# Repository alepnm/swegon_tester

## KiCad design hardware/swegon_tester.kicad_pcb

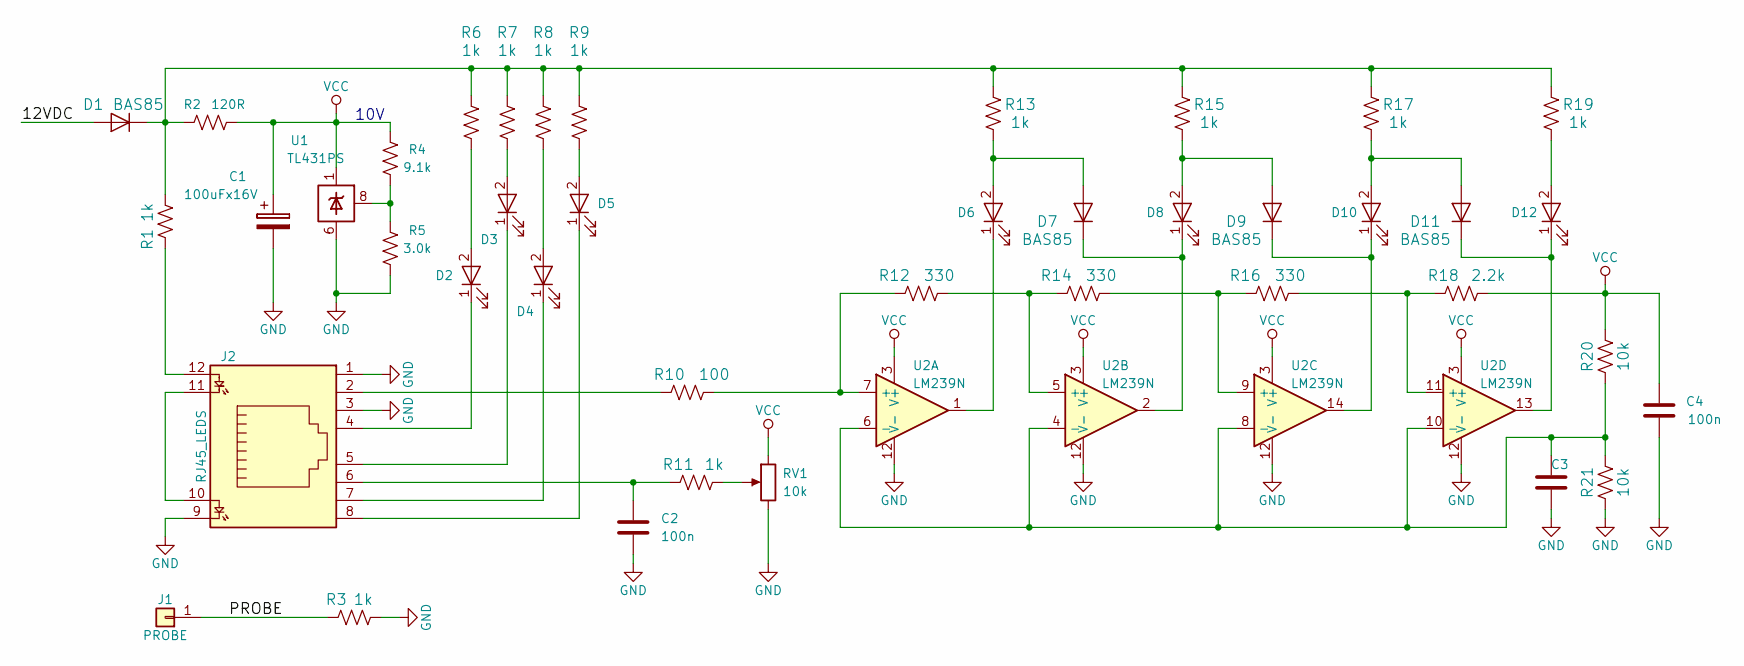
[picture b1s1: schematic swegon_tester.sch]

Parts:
C1: 100uFx16V; CP_Radial_D6.3mm_P2.50mm
C2, C3, C4: 100n; C_0805
D1, D7, D9, D11: BAS85; D_MiniMELF
D2: PIN4; LED_D3.0mm
D3: PIN5; LED_D3.0mm
D4: PIN7; LED_D3.0mm
D5: PIN8; LED_D3.0mm
D6: 2.6K; LED_D3.0mm
D8: 1.9K; LED_D3.0mm
D10: 1.2K; LED_D3.0mm
D12: 680R; LED_D3.0mm
J1: PROBE; SolderWirePad_2x_1mmDrill
J2: RJ45_LEDS; RJHSE538X
R1, R3, R6, R7, R8, R9, R11, R13, R15, R17, R19: 1k; R_0805
R2: 120R; R_1206
R4: 9.1k; R_0805
R5: 3.0k; R_0805
R10: 100; R_0805
R12, R14, R16: 330; R_0805
R18: 2.2k; R_0805
R20, R21: 10k; R_0805
RV1: 10k; Potentiometer_Trimmer_ACP_CA6v_Horizontal
U1: TL431PS; SOIC-8_3.9x4.9mm_Pitch1.27mm
U2: LM239N; DIP-14_W7.62mm

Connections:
/12VDC: D1.2 (A)
/PROBE: J1.1, R3.1
GND: C1.2, C2.2, C3.1, C4.1, J2.1, J2.3, J2.9, R3.2, R5.1, R21.1, RV1.3, U1.2, U1.3, U1.6 (A), U1.7, U2.12 (V-)
unnamed: C2.1, J2.6, R11.1
unnamed: C3.2, R20.1, R21.2, U2.4 (-), U2.6 (-), U2.8 (-), U2.10 (-)
unnamed: D1.1 (K), R1.2, R2.1, R6.2, R7.2, R8.2, R9.2, R13.2, R15.2, R17.2, R19.2
unnamed: D2.1 (K), J2.4
unnamed: D2.2 (A), R6.1
unnamed: D3.1 (K), J2.5
unnamed: D3.2 (A), R7.1
unnamed: D4.1 (K), J2.7
unnamed: D4.2 (A), R8.1
unnamed: D5.1 (K), J2.8
unnamed: D5.2 (A), R9.1
unnamed: D6.1 (K), U2.1
unnamed: D6.2 (A), D7.2 (A), R13.1
unnamed: D7.1 (K), D8.1 (K), U2.2
unnamed: D8.2 (A), D9.2 (A), R15.1
unnamed: D9.1 (K), D10.1 (K), U2.14
unnamed: D10.2 (A), D11.2 (A), R17.1
unnamed: D11.1 (K), D12.1 (K), U2.13
unnamed: D12.2 (A), R19.1
unnamed: J2.2, R10.1
unnamed: J2.10, J2.11
unnamed: J2.12, R1.1
unnamed: R4.1, R5.2, U1.8 (G)
unnamed: R10.2, R12.1, U2.7 (+)
unnamed: R11.2, RV1.2
unnamed: R12.2, R14.1, U2.5 (+)
unnamed: R14.2, R16.1, U2.9 (+)
unnamed: R16.2, R18.1, U2.11 (+)
VCC: C1.1, C4.2, R2.2, R4.2, R18.2, R20.2, RV1.1, U1.1 (C), U2.3 (V+)

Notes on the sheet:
10V

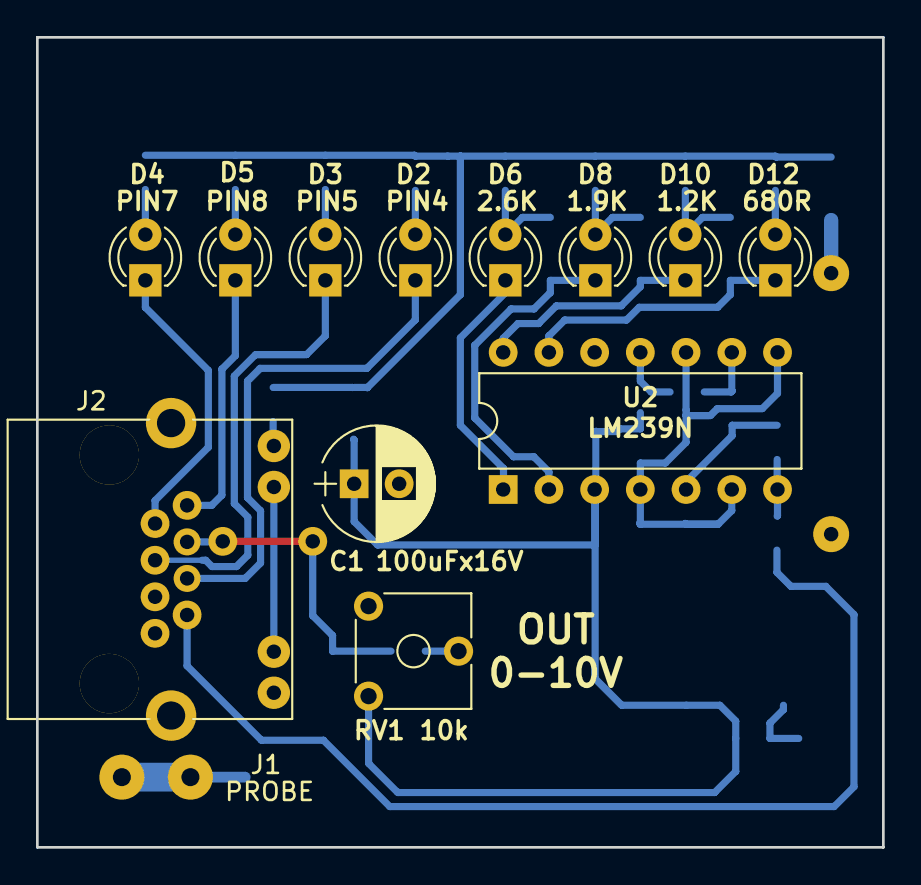
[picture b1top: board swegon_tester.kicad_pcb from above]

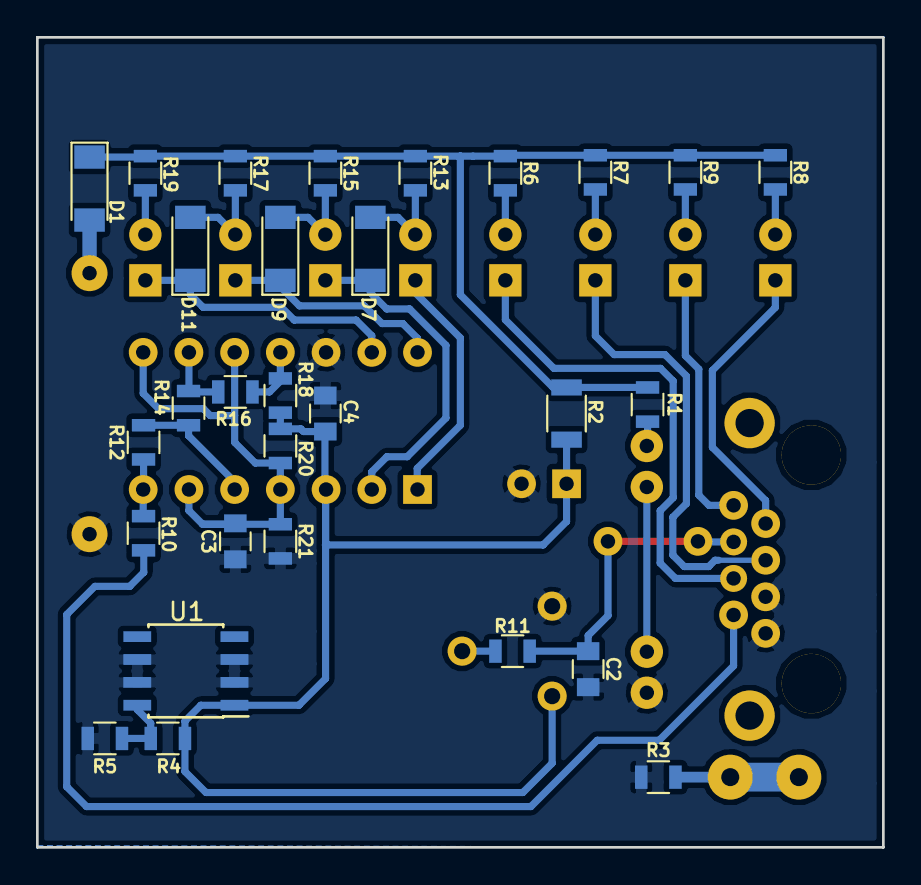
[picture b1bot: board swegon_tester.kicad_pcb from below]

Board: 2 copper layers, 47.0 x 45.0 mm, 42 parts (29 on the bottom side), 31 nets.

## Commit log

2018-07-03 pradine inicializacija
